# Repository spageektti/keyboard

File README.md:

# keyboard
Small keyboard with few mechanical switches, a rotary encoder and a small OLED screen powered by RP2040

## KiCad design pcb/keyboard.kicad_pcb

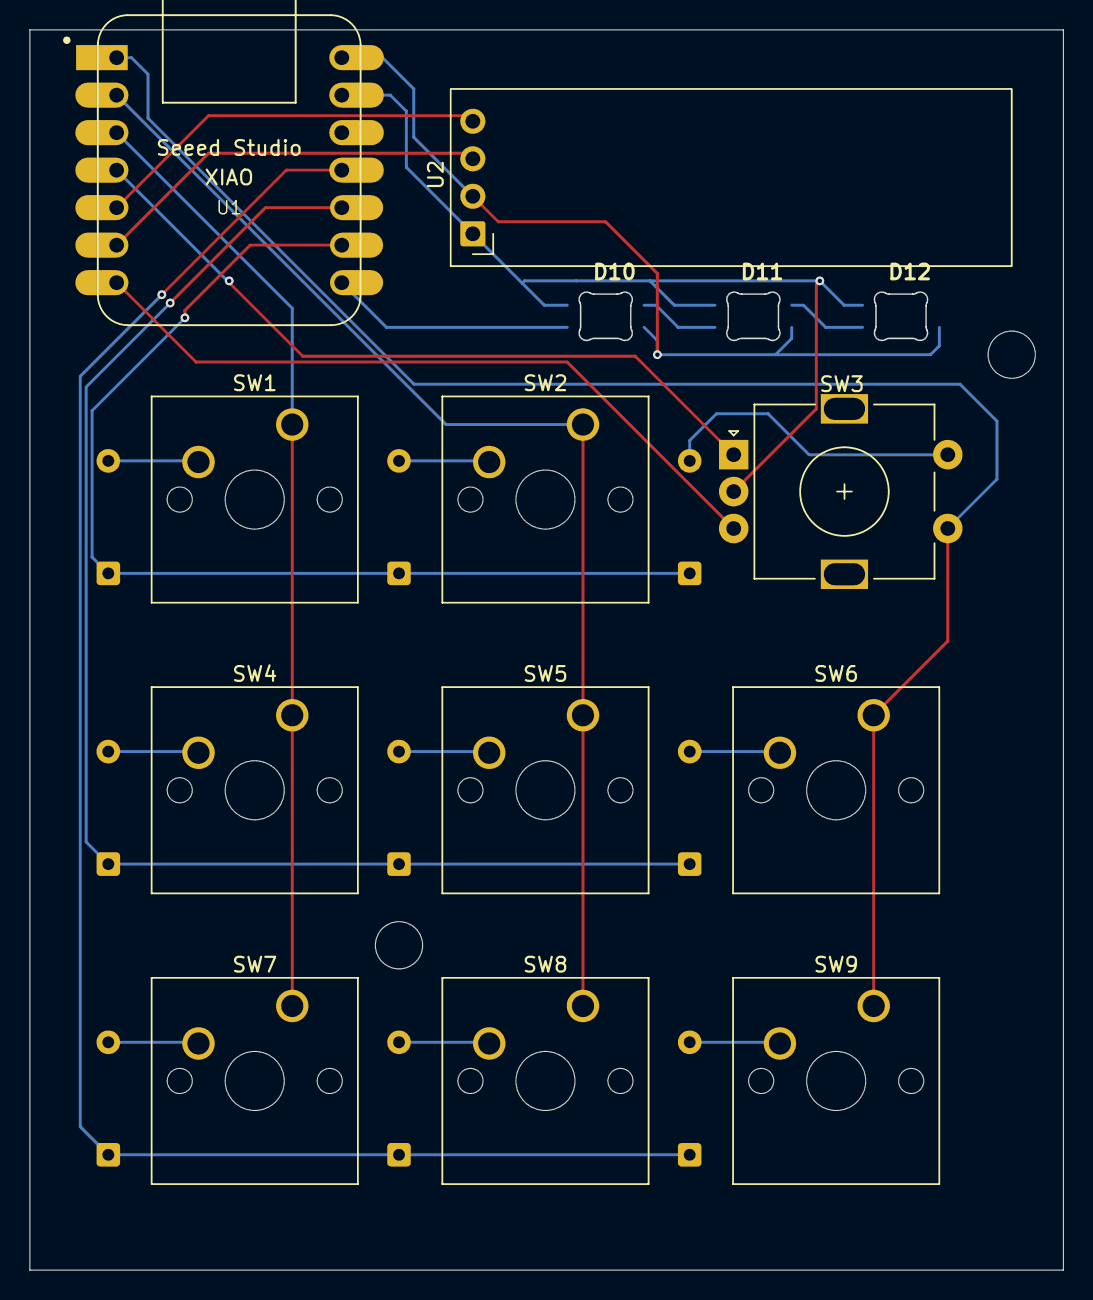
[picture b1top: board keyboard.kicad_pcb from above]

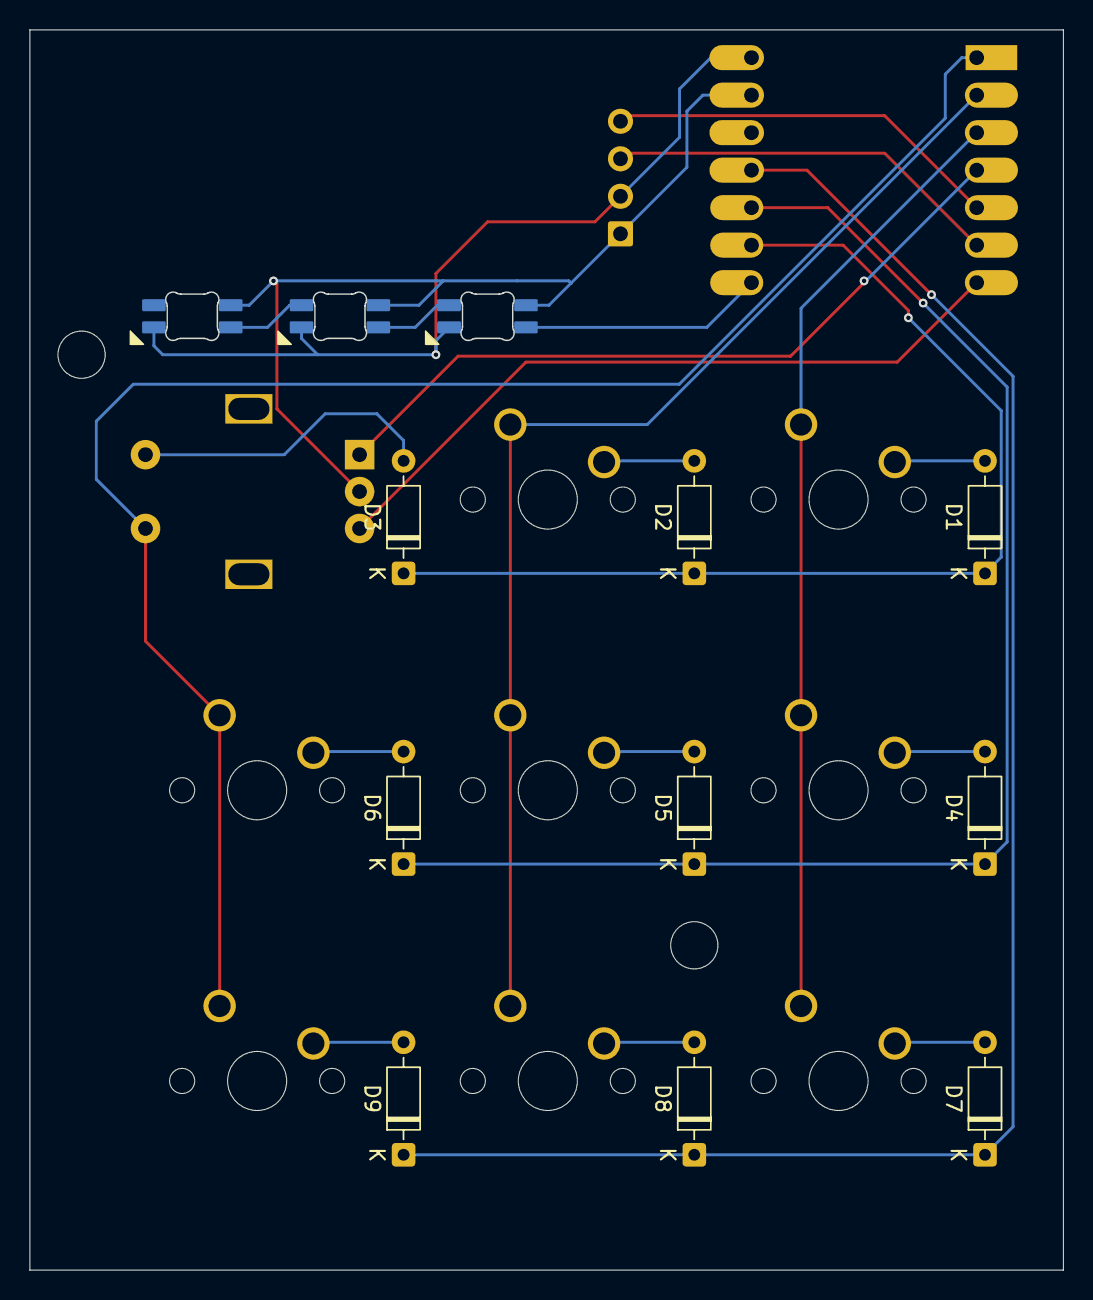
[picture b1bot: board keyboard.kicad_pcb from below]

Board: 2 copper layers, 69.9 x 83.9 mm, 23 parts (9 on the bottom side), 24 nets.

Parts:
D1, D2, D3, D4, D5, D6, D7, D8, D9: 1N4148; D_DO-35_SOD27_P7.62mm_Horizontal
D10, D11, D12: SK6812MINI-E; SK6812MINI-E_fixed
SW1, SW2, SW4, SW5, SW6, SW7, SW8, SW9: SW_Push; SW_Cherry_MX_1.00u_PCB
SW3: RotaryEncoder_Switch; RotaryEncoder_Alps_EC11E-Switch_Vertical_H20mm
U1: MODULE-SEEEDUINO-XIAO-RP2040; XIAO-Generic-Hybrid-14P-2.54-21X17.8MM
U2: ER_OLEDM0.91_1x-I2C

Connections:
Column 0: SW1.1, SW4.1, SW7.1, U1.3 (PA10_A2_D2)
Column 1: SW2.1, SW5.1, SW8.1, U1.2 (PA4_A1_D1)
Column 2: SW3.S1, SW6.1, SW9.1, U1.1 (PA02_A0_D0)
GND: D10.1 (VSS), D11.1 (VSS), D12.1 (VSS), SW3.C, U1.13 (GND), U2.1 (GND)
unnamed: D1.2 (A), SW1.2
unnamed: D2.2 (A), SW2.2
unnamed: D4.2 (A), SW4.2
unnamed: D5.2 (A), SW5.2
unnamed: D6.2 (A), SW6.2
unnamed: D7.2 (A), SW7.2
unnamed: D8.2 (A), SW8.2
unnamed: D9.2 (A), SW9.2
unnamed: D10.4 (DOUT), D11.2 (DIN)
unnamed: D11.4 (DOUT), D12.2 (DIN)
RGB LEDs: D10.2 (DIN), U1.8 (PB09_A7_D7_RX)
ROT A: SW3.A, U1.4 (PA11_A3_D3)
ROT B: SW3.B, U1.7 (PB08_A6_D6_TX)
ROT S2: D3.2 (A), SW3.S2
Row 0: D1.1 (K), D2.1 (K), D3.1 (K), U1.9 (PA7_A8_D8_SCK)
Row 1: D4.1 (K), D5.1 (K), D6.1 (K), U1.10 (PA5_A9_D9_MISO)
Row 2: D7.1 (K), D8.1 (K), D9.1 (K), U1.11 (PA6_A10_D10_MOSI)
SCL: U1.6 (PA9_A5_D5_SCL), U2.3 (SCL)
SDA: U1.5 (PA8_A4_D4_SDA), U2.4 (SDA)
VCC: D10.3 (VDD), D11.3 (VDD), D12.3 (VDD), U1.14 (5V), U2.2 (VCC)

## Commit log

2026-06-09 add all the elements to the schematic and the pcb
2026-06-09 connect switches to the microcontroller
2026-06-09 connect all components on schematic; remove invalid connections on pcb
2026-06-09 connect everything on the pcb
2026-06-09 add schematic pdf export
2026-06-10 add rgb leds to schematic; update power labels; remove a switch and add rotary knob one to matrix instead
2026-06-10 connect everything on the schematic
2026-06-10 align switches, board and screen on the pcb
2026-06-10 make the board smaller, add third rgb
2026-06-10 improve schematic layout
2026-06-10 align diodes
2026-06-10 align diodes in a better way
2026-06-10 align diodes correctly and connect them to the switches and in rows/columns
2026-06-10 swap columns gpio pins for easier pcb routing
2026-06-10 finish the pcb
